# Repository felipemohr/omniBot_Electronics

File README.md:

## OmniBot Electronics

This repository contains the **[omniBot](https://github.com/felipemohr/omniBot)** PCB project.

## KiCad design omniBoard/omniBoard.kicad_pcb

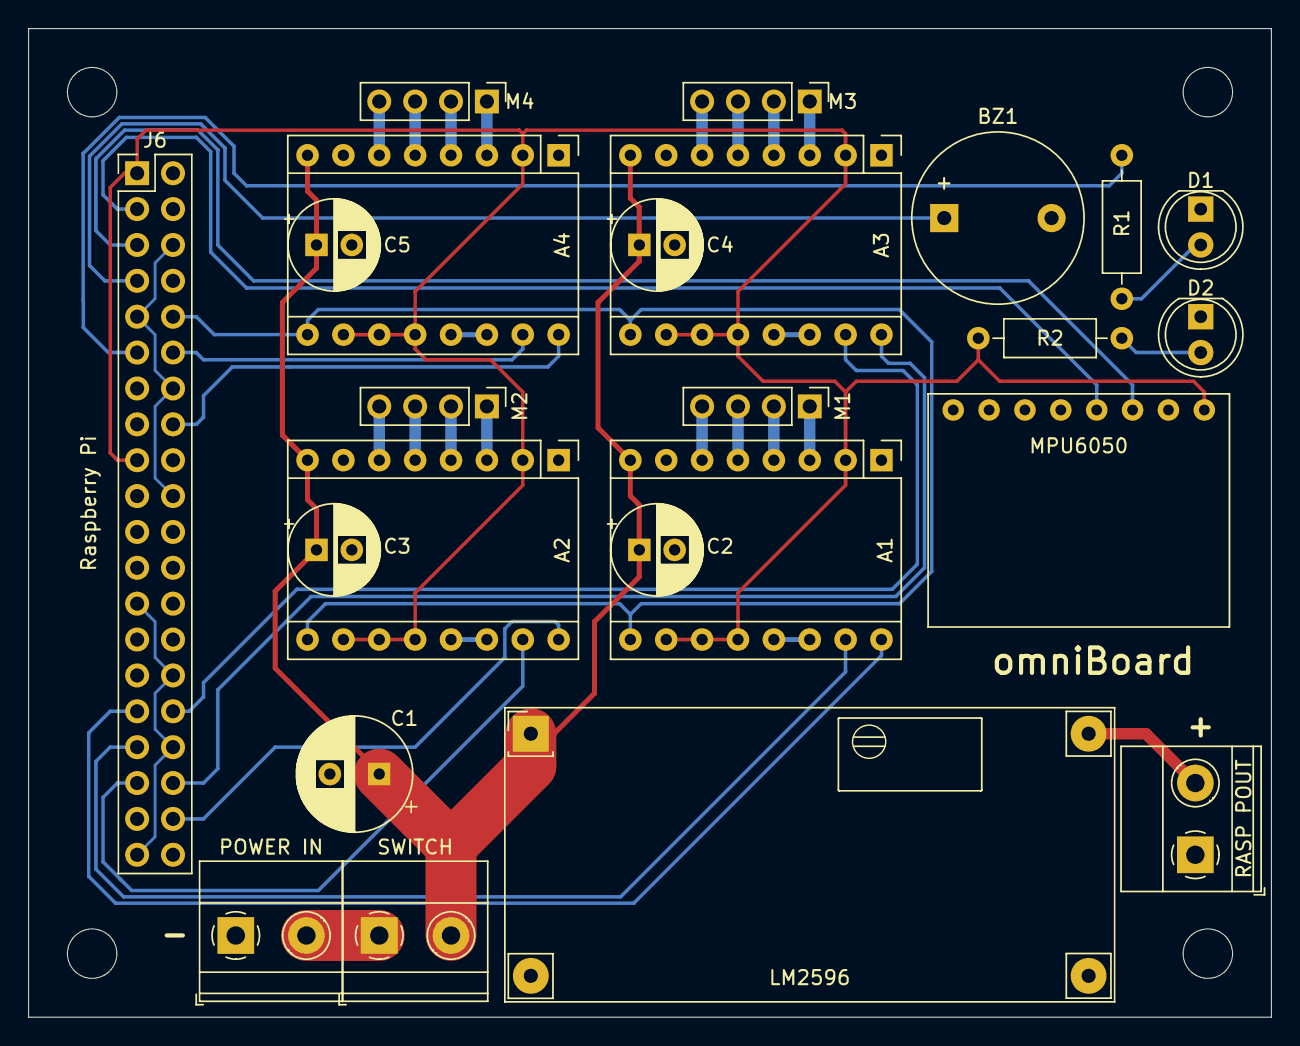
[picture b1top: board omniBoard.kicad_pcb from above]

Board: 2 copper layers, 88.0 x 70.0 mm, 24 parts (0 on the bottom side), 40 nets.

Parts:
A1, A2, A3, A4: Pololu_Breakout_A4988; Pololu_Breakout-16_15.2x20.3mm
BZ1: Buzzer; Buzzer_12x9.5RM7.6
C1: 220uF; CP_Radial_D8.0mm_P3.50mm
C2, C3, C4, C5: 100uF; CP_Radial_D6.3mm_P2.50mm
D1, D2: LED; LED_D5.0mm
J6: Raspberry Pi; PinHeader_2x20_P2.54mm_Vertical
LM2596: LM2596_module
M1, M2, M3, M4: Conn_01x04; PinHeader_1x04_P2.54mm_Vertical
MPU6050: MPU6050_module
POWER IN: Conn_01x02; TerminalBlock_Phoenix_MKDS-1,5-2_1x02_P5.00mm_Horizontal
R1, R2: 68; R_Axial_DIN0207_L6.3mm_D2.5mm_P10.16mm_Horizontal
RASP POUT: Conn_01x02; TerminalBlock_Phoenix_MKDS-1,5-2-5.08_1x02_P5.08mm_Horizont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
SWITCH: Conn_01x02; TerminalBlock_Phoenix_MKDS-1,5-2-5.08_1x02_P5.08mm_Horizont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

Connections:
+3V3: A1.2, A1.10, A1.11, A1.12, A2.2, A2.10, A2.11, A2.12, A3.2, A3.10, A3.11, A3.12, A4.2, A4.10, A4.11, A4.12, J6.1, J6.17, MPU6050.1, R2.2
+5V: LM2596.4, RASP POUT.2
+12V: A1.8, A2.8, A3.8, A4.8, C1.1, C2.1, C3.1, C4.1, C5.1, LM2596.1, SWITCH.2
/BUZZER: BZ1.1, J6.7
/LED: J6.11, R1.2
/M0_1A: A1.4, M1.2
/M0_1B: A1.3, M1.1
/M0_2A: A1.5, M1.3
/M0_2B: A1.6, M1.4
/M0_DIR: A1.16, J6.31
/M0_STEP: A1.15, J6.33
/M1_1A: A2.4, M2.2
/M1_1B: A2.3, M2.1
/M1_2A: A2.5, M2.3
/M1_2B: A2.6, M2.4
/M1_DIR: A2.16, J6.38
/M1_STEP: A2.15, J6.35
/M2_1A: A3.4, M3.2
/M2_1B: A3.3, M3.1
/M2_2A: A3.5, M3.3
/M2_2B: A3.6, M3.4
/M2_DIR: A3.16, J6.36
/M2_STEP: A3.15, J6.32
/M3_1A: A4.4, M4.2
/M3_1B: A4.3, M4.1
/M3_2A: A4.5, M4.3
/M3_2B: A4.6, M4.4
/M3_DIR: A4.16, J6.16
/M3_STEP: A4.15, J6.12
/SCL: J6.5, MPU6050.3
/SDA: J6.3, MPU6050.4
/_ENABLE: A1.9, A2.9, A3.9, A4.9, J6.10
/_RESET0: A1.13, A1.14
/_RESET1: A2.13, A2.14
/_RESET2: A3.13, A3.14
/_RESET3: A4.13, A4.14
GND: A1.1, A1.7, A2.1, A2.7, A3.1, A3.7, A4.1, A4.7, BZ1.2, C1.2, C2.2, C3.2, C4.2, C5.2, D1.1, D2.1, J6.6, J6.9, J6.14, J6.20, J6.25, J6.30, J6.34, J6.39, LM2596.2, LM2596.3, MPU6050.2, POWER IN.1, RASP POUT.1
unnamed: D1.2, R1.1
unnamed: D2.2, R2.1
unnamed: POWER IN.2, SWITCH.1

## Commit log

2021-12-24 Create schematics
2021-12-25 Add footprints and ADC
2021-12-25 Place components on the board
2021-12-25 Update 3d models
2021-12-26 Remove useless components
2021-12-26 Finish board 1st version
2021-12-26 Finish board 2nd version
2021-12-28 Add new led
2021-12-31 Final version
